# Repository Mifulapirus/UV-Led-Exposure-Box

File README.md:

# README #

UV LED exposure box

### What is this repository for? ###

* This project contains all the required information, hardware and software to make your own UV LED exposure machine so you can create your own PCBs at home.

### Materials ###
* Here is the list of all the different parts you need to build your own UV-LED Exposure Box
* https://docs.google.com/spreadsheets/d/1VbFTGXd1PagAe3uoOmZKsPFVGucdBjDqCyi8I9-2VKY/edit?usp=sharing

### Contact ###
* @mifulapirus

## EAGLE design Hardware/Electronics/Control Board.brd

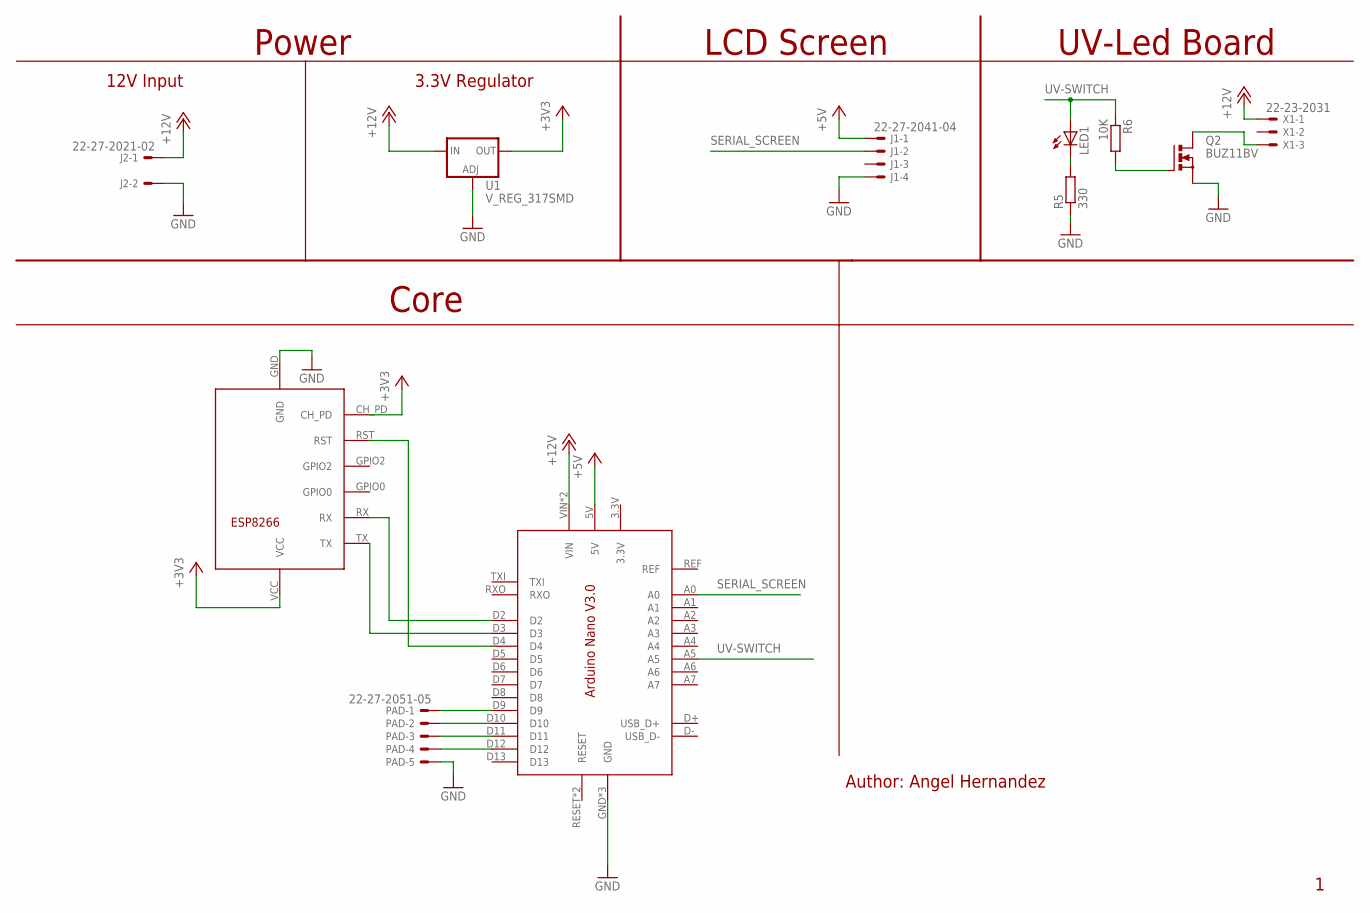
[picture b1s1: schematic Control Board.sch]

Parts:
J1: 22-27-2041-04; 6410-04
J2: 22-27-2021-02; 6410-02
LED1: LED3MM
PAD: 22-27-2051-05; 6410-05
Q2: BUZ11BV; TO220BV
R5: 330; 0204/7
R6: 10K; 0204/7
U1: V_REG_317SMD; SOT223
U$1: ARDUINO_NANO_V3
U$2: ESP8266
X1: 22-23-2031

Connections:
+3V3: U1.2 (OUT), U$2.CH_PD, U$2.VCC
+5V: J1.1, U$1.5V
+12V: J2.1, U1.3 (IN), U$1.VIN, U$1.VUSB (VIN), X1.1
GND: J1.4, J2.2, PAD.5, Q2.S, R5.1, U1.1 (ADJ), U$1.GND, U$1.GND1 (GND), U$1.GND_USB (GND), U$2.GND
unnamed: Q2.D, X1.3
unnamed: U$1.D3, U$2.TX
unnamed: U$1.D2, U$2.RX
unnamed: PAD.1, U$1.D9
unnamed: PAD.2, U$1.D10
unnamed: PAD.3, U$1.D11
unnamed: PAD.4, U$1.D12
unnamed: LED1.K (C), R5.2
unnamed: Q2.G, R6.2
unnamed: U$1.D4, U$2.RST
SERIAL_SCREEN: J1.2, U$1.A0
UV-SWITCH: LED1.A, R6.1, U$1.A5

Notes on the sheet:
UV-Led Board
Power
LCD Screen
Author: Angel Hernandez
12V Input
3.3V Regulator
Core

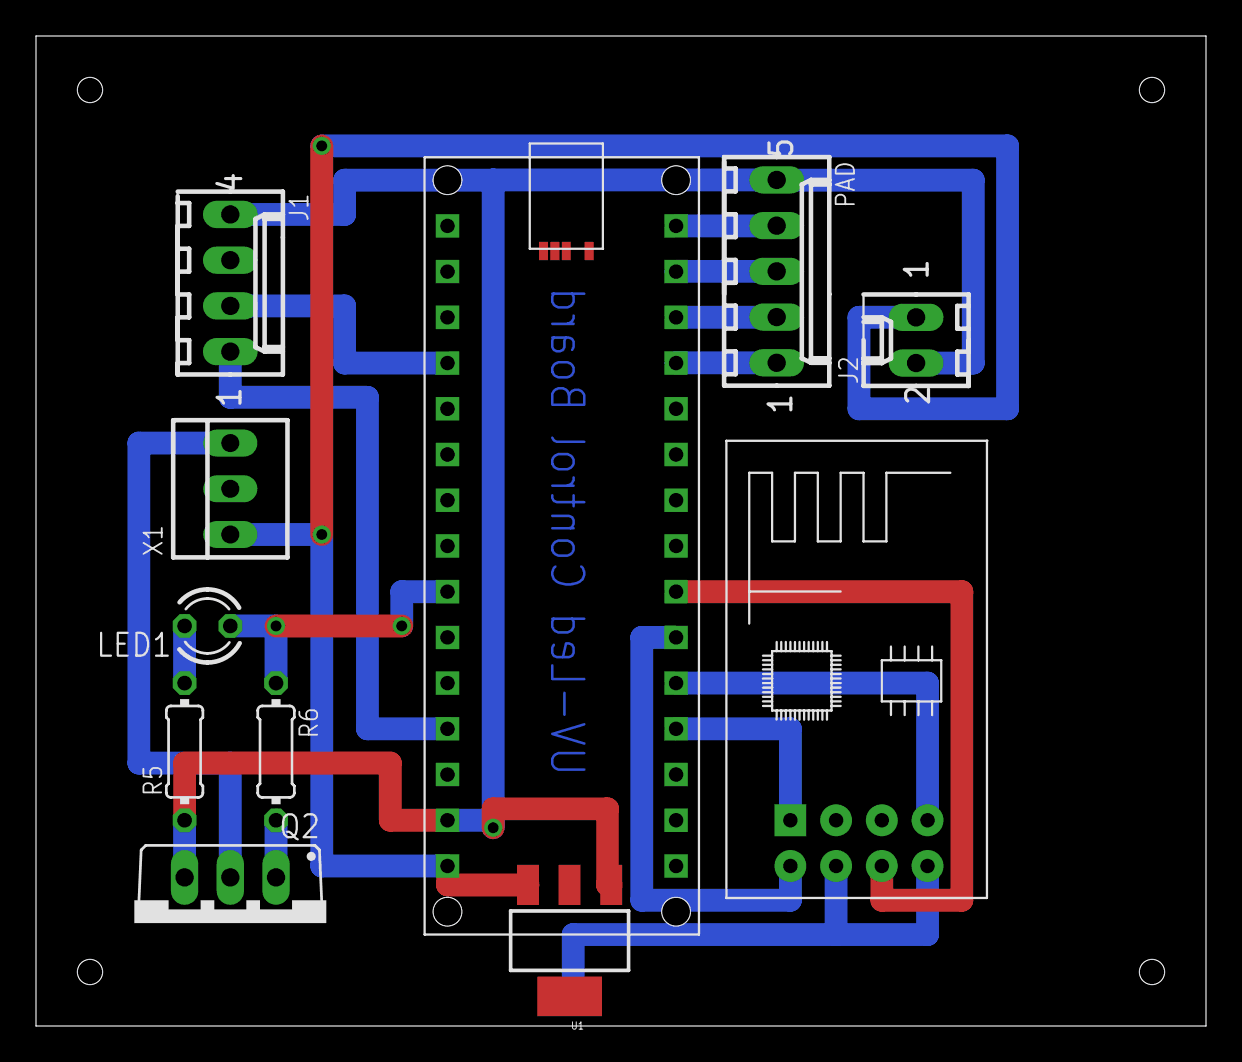
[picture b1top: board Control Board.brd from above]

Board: 2 copper layers, 65.0 x 55.0 mm, 11 parts (0 on the bottom side), 16 nets.

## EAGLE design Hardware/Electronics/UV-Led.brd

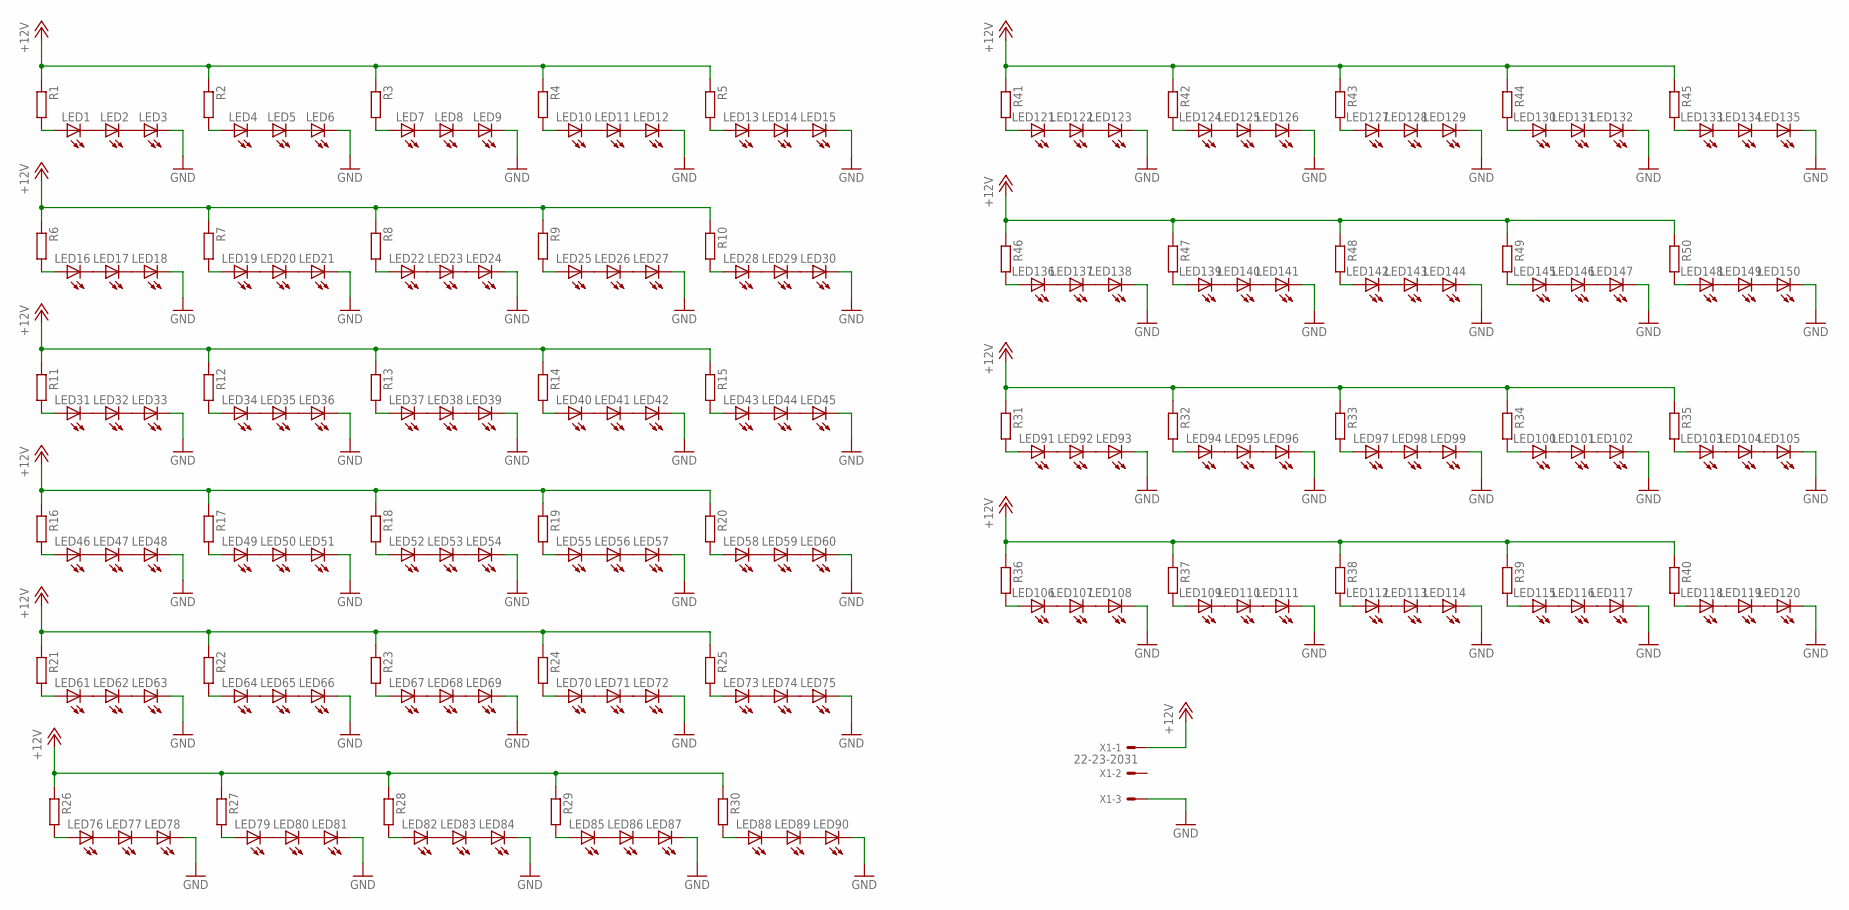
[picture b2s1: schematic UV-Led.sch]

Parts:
LED1, LED2, LED3, LED4, LED5, LED6, LED7, LED8, LED9, LED10, LED11, LED12, LED13, LED14, LED15, LED16, LED17, LED18, LED19, LED20, LED21, LED22, LED23, LED24, LED25, LED26, LED27, LED28, LED29, LED30, LED31, LED32, LED33, LED34, LED35, LED36, LED37, LED38, LED39, LED40, LED41, LED42, LED43, LED44, LED45, LED46, LED47, LED48, LED49, LED50, LED51, LED52, LED53, LED54, LED55, LED56, LED57, LED58, LED59, LED60, LED61, LED62, LED63, LED64, LED65, LED66, LED67, LED68, LED69, LED70, LED71, LED72, LED73, LED74, LED75, LED76, LED77, LED78, LED79, LED80, LED81, LED82, LED83, LED84, LED85, LED86, LED87, LED88, LED89, LED90, LED91, LED92, LED93, LED94, LED95, LED96, LED97, LED98, LED99, LED100, LED101, LED102, LED103, LED104, LED105, LED106, LED107, LED108, LED109, LED110, LED111, LED112, LED113, LED114, LED115, LED116, LED117, LED118, LED119, LED120, LED121, LED122, LED123, LED124, LED125, LED126, LED127, LED128, LED129, LED130, LED131, LED132, LED133, LED134, LED135, LED136, LED137, LED138, LED139, LED140, LED141, LED142, LED143, LED144, LED145, LED146, LED147, LED148, LED149, LED150: LED5MM
R1, R2, R3, R4, R5, R6, R7, R8, R9, R10, R11, R12, R13, R14, R15, R16, R17, R18, R19, R20, R21, R22, R23, R24, R25, R26, R27, R28, R29, R30, R31, R32, R33, R34, R35, R36, R37, R38, R39, R40, R41, R42, R43, R44, R45, R46, R47, R48, R49, R50: R-EU_0207/10; 0207/10
X1: 22-23-2031

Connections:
+12V: R1.1, R2.1, R3.1, R4.1, R5.1, R6.1, R7.1, R8.1, R9.1, R10.1, R11.1, R12.1, R13.1, R14.1, R15.1, R16.1, R17.1, R18.1, R19.1, R20.1, R21.1, R22.1, R23.1, R24.1, R25.1, R26.1, R27.1, R28.1, R29.1, R30.1, R31.1, R32.1, R33.1, R34.1, R35.1, R36.1, R37.1, R38.1, R39.1, R40.1, R41.1, R42.1, R43.1, R44.1, R45.1, R46.1, R47.1, R48.1, R49.1, R50.1, X1.1
GND: LED3.K (C), LED6.K (C), LED9.K (C), LED12.K (C), LED15.K (C), LED18.K (C), LED21.K (C), LED24.K (C), LED27.K (C), LED30.K (C), LED33.K (C), LED36.K (C), LED39.K (C), LED42.K (C), LED45.K (C), LED48.K (C), LED51.K (C), LED54.K (C), LED57.K (C), LED60.K (C), LED63.K (C), LED66.K (C), LED69.K (C), LED72.K (C), LED75.K (C), LED78.K (C), LED81.K (C), LED84.K (C), LED87.K (C), LED90.K (C), LED93.K (C), LED96.K (C), LED99.K (C), LED102.K (C), LED105.K (C), LED108.K (C), LED111.K (C), LED114.K (C), LED117.K (C), LED120.K (C), LED123.K (C), LED126.K (C), LED129.K (C), LED132.K (C), LED135.K (C), LED138.K (C), LED141.K (C), LED144.K (C), LED147.K (C), LED150.K (C), X1.3
unnamed: LED1.K (C), LED2.A
unnamed: LED2.K (C), LED3.A
unnamed: LED4.K (C), LED5.A
unnamed: LED5.K (C), LED6.A
unnamed: LED7.K (C), LED8.A
unnamed: LED8.K (C), LED9.A
unnamed: LED1.A, R1.2
unnamed: LED4.A, R2.2
unnamed: LED7.A, R3.2
unnamed: LED13.K (C), LED14.A
unnamed: LED10.K (C), LED11.A
unnamed: LED11.K (C), LED12.A
unnamed: LED10.A, R4.2
unnamed: LED14.K (C), LED15.A
unnamed: LED13.A, R5.2
unnamed: LED16.K (C), LED17.A
unnamed: LED17.K (C), LED18.A
unnamed: LED19.K (C), LED20.A
unnamed: LED20.K (C), LED21.A
unnamed: LED22.K (C), LED23.A
unnamed: LED23.K (C), LED24.A
unnamed: LED16.A, R6.2
unnamed: LED19.A, R7.2
unnamed: LED22.A, R8.2
unnamed: LED25.K (C), LED26.A
unnamed: LED26.K (C), LED27.A
unnamed: LED28.K (C), LED29.A
unnamed: LED29.K (C), LED30.A
unnamed: LED25.A, R9.2
unnamed: LED28.A, R10.2
unnamed: LED31.K (C), LED32.A
unnamed: LED32.K (C), LED33.A
unnamed: LED34.K (C), LED35.A
unnamed: LED35.K (C), LED36.A
unnamed: LED37.K (C), LED38.A
unnamed: LED38.K (C), LED39.A
unnamed: LED31.A, R11.2
unnamed: LED34.A, R12.2
unnamed: LED37.A, R13.2
unnamed: LED40.K (C), LED41.A
unnamed: LED41.K (C), LED42.A
unnamed: LED43.K (C), LED44.A
unnamed: LED44.K (C), LED45.A
unnamed: LED40.A, R14.2
unnamed: LED43.A, R15.2
unnamed: LED46.K (C), LED47.A
unnamed: LED47.K (C), LED48.A
unnamed: LED49.K (C), LED50.A
unnamed: LED50.K (C), LED51.A
unnamed: LED52.K (C), LED53.A
unnamed: LED53.K (C), LED54.A
unnamed: LED46.A, R16.2
unnamed: LED49.A, R17.2
unnamed: LED52.A, R18.2
unnamed: LED55.K (C), LED56.A
unnamed: LED56.K (C), LED57.A
unnamed: LED58.K (C), LED59.A
unnamed: LED59.K (C), LED60.A
unnamed: LED55.A, R19.2
unnamed: LED58.A, R20.2
unnamed: LED61.K (C), LED62.A
unnamed: LED62.K (C), LED63.A
unnamed: LED64.K (C), LED65.A
unnamed: LED65.K (C), LED66.A
unnamed: LED67.K (C), LED68.A
unnamed: LED68.K (C), LED69.A
unnamed: LED61.A, R21.2
unnamed: LED64.A, R22.2
unnamed: LED67.A, R23.2
unnamed: LED70.K (C), LED71.A
unnamed: LED71.K (C), LED72.A
unnamed: LED73.K (C), LED74.A
unnamed: LED74.K (C), LED75.A
unnamed: LED70.A, R24.2
unnamed: LED73.A, R25.2
unnamed: LED76.K (C), LED77.A
unnamed: LED77.K (C), LED78.A
unnamed: LED79.K (C), LED80.A
unnamed: LED80.K (C), LED81.A
unnamed: LED82.K (C), LED83.A
unnamed: LED83.K (C), LED84.A
unnamed: LED76.A, R26.2
unnamed: LED79.A, R27.2
unnamed: LED82.A, R28.2
unnamed: LED85.K (C), LED86.A
unnamed: LED86.K (C), LED87.A
unnamed: LED88.K (C), LED89.A
unnamed: LED89.K (C), LED90.A
unnamed: LED85.A, R29.2
unnamed: LED88.A, R30.2
unnamed: LED91.K (C), LED92.A
unnamed: LED92.K (C), LED93.A
unnamed: LED94.K (C), LED95.A
unnamed: LED95.K (C), LED96.A
unnamed: LED97.K (C), LED98.A
unnamed: LED98.K (C), LED99.A
unnamed: LED91.A, R31.2
unnamed: LED94.A, R32.2
unnamed: LED97.A, R33.2
unnamed: LED100.K (C), LED101.A
unnamed: LED101.K (C), LED102.A
unnamed: LED103.K (C), LED104.A
unnamed: LED104.K (C), LED105.A
unnamed: LED100.A, R34.2
unnamed: LED103.A, R35.2
unnamed: LED106.K (C), LED107.A
unnamed: LED107.K (C), LED108.A
unnamed: LED109.K (C), LED110.A
unnamed: LED110.K (C), LED111.A
unnamed: LED112.K (C), LED113.A
unnamed: LED113.K (C), LED114.A
unnamed: LED106.A, R36.2
unnamed: LED109.A, R37.2
unnamed: LED112.A, R38.2
unnamed: LED115.K (C), LED116.A
unnamed: LED116.K (C), LED117.A
unnamed: LED118.K (C), LED119.A
unnamed: LED119.K (C), LED120.A
unnamed: LED115.A, R39.2
unnamed: LED118.A, R40.2
unnamed: LED121.K (C), LED122.A
unnamed: LED122.K (C), LED123.A
unnamed: LED124.K (C), LED125.A
unnamed: LED125.K (C), LED126.A
unnamed: LED127.K (C), LED128.A
unnamed: LED128.K (C), LED129.A
unnamed: LED121.A, R41.2
unnamed: LED124.A, R42.2
unnamed: LED127.A, R43.2
unnamed: LED130.K (C), LED131.A
unnamed: LED131.K (C), LED132.A
unnamed: LED133.K (C), LED134.A
unnamed: LED134.K (C), LED135.A
unnamed: LED130.A, R44.2
unnamed: LED133.A, R45.2
unnamed: LED136.K (C), LED137.A
unnamed: LED137.K (C), LED138.A
unnamed: LED139.K (C), LED140.A
unnamed: LED140.K (C), LED141.A
unnamed: LED142.K (C), LED143.A
unnamed: LED143.K (C), LED144.A
unnamed: LED136.A, R46.2
unnamed: LED139.A, R47.2
unnamed: LED142.A, R48.2
unnamed: LED145.K (C), LED146.A
unnamed: LED146.K (C), LED147.A
unnamed: LED148.K (C), LED149.A
unnamed: LED149.K (C), LED150.A
unnamed: LED145.A, R49.2
unnamed: LED148.A, R50.2

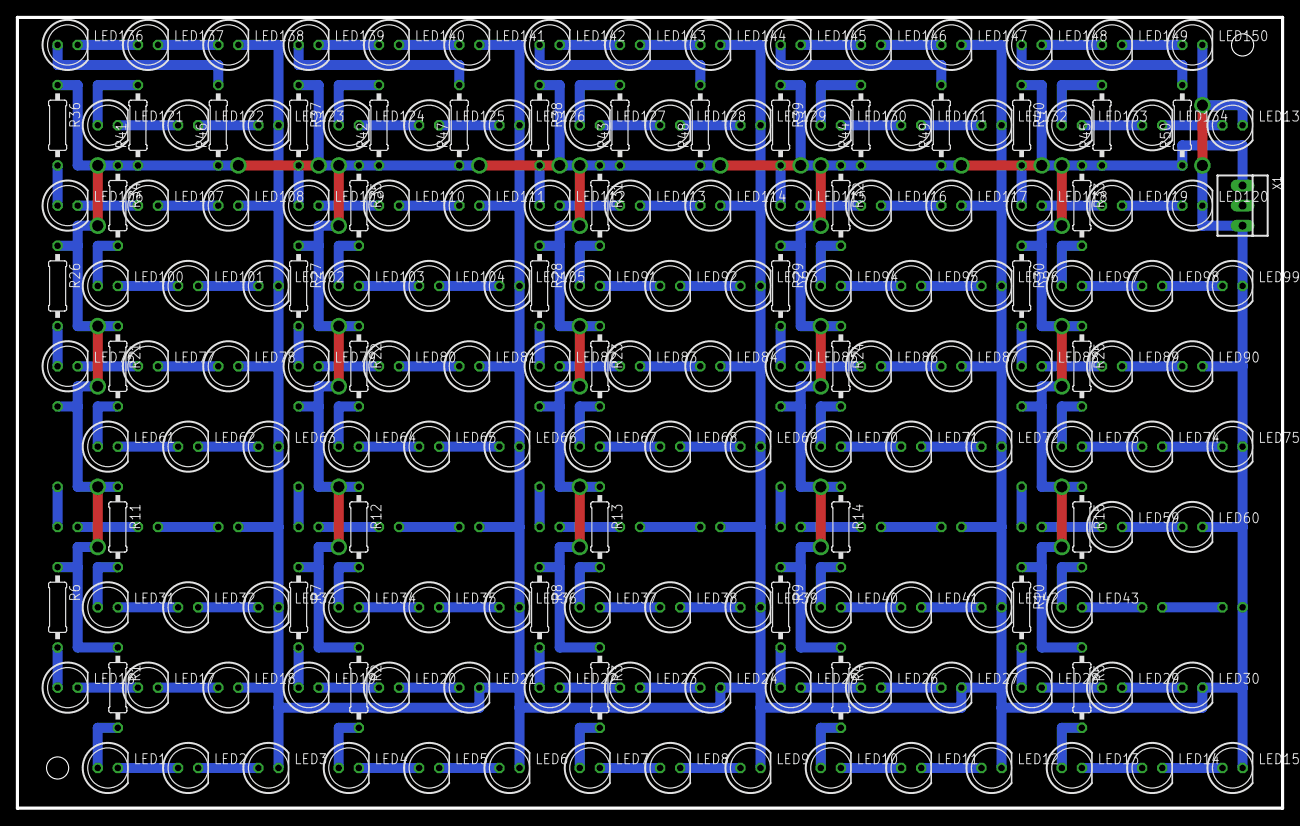
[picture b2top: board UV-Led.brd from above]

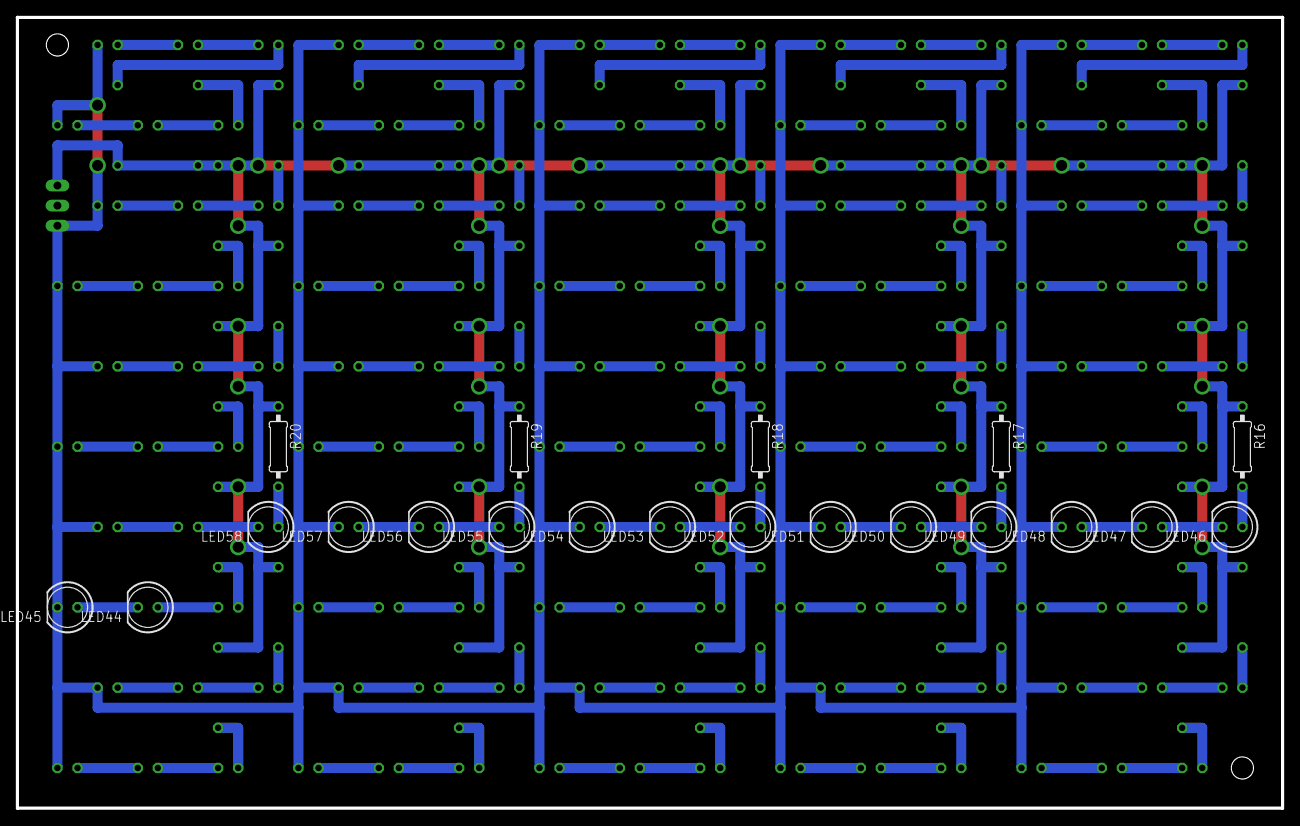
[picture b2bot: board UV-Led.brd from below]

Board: 2 copper layers, 160.0 x 100.0 mm, 201 parts (20 on the bottom side), 152 nets.

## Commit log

2015-02-05 Initial commit - Bottom side of the box
2015-02-05 Electronics - Initial version of the UV-Led board
2015-02-06 Electronics - Control board Rev.0
2015-02-07 Firmware - Initial firmware commit
2015-02-07 Intermediate commit - needs improvement
2015-02-07 Electronics - Working version
2015-02-09 Regular Commit - Added Support for ESP8266 - Added Commands - Bug fixes
2015-02-10 Regular Commit - Cleaned up some code
2015-02-15 Regular Commit - Moved some variables

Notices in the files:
parts and their libraries:
SparkFun-PowerIC: Licensing: Creative Commons ShareAlike 4.0 International - https://creativecommons.org/licenses/by-sa/4.0
